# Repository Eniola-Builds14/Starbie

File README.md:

# Starbie
Starbie is a little robot pet with a star shaped PCB. It was designed using KICAD .I had alot of fun while building it and  I learned new things along the way. Starbie is a small project, but its my first step into PCB design.

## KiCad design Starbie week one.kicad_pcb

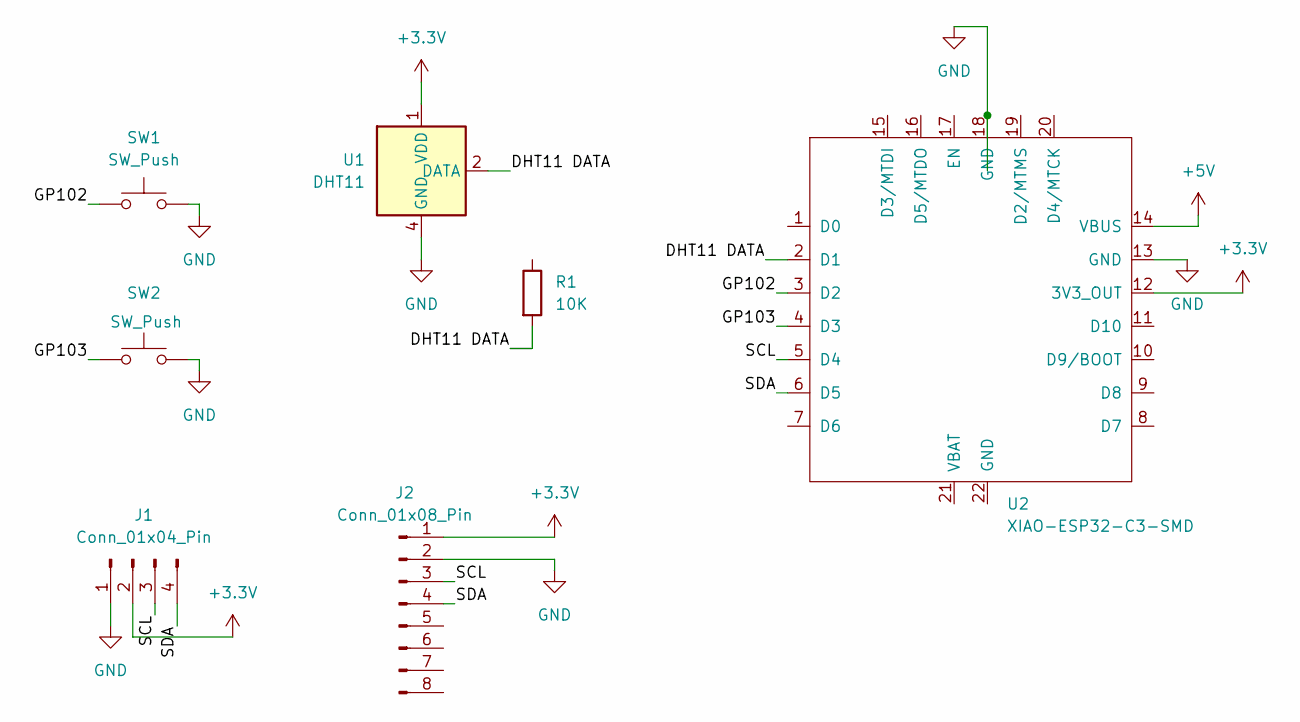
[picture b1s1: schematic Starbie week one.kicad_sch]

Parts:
J1: Conn_01x04_Pin; Display_128x64_096_I2C
J2: Conn_01x08_Pin; PinHeader_1x08_P2.54mm_Vertical
R1: 10K; R_Axial_DIN0204_L3.6mm_D1.6mm_P7.62mm_Horizontal
SW1, SW2: SW_Push; SW_Cherry_MX_1.00u_PCB
U1: DHT11; Aosong_DHT11_5.5x12.0_P2.54mm
U2: XIAO-ESP32-C3-SMD

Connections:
+3.3V: J1.2, J2.1, U1.1 (VDD), U2.12 (3V3_OUT)
+5V: U2.14 (VBUS)
/<NO NET>: SW2.1, U2.4 (D3)
/DHT11 DATA: R1.2, U1.2 (DATA), U2.2 (D1)
/GP102: SW1.1, U2.3 (D2)
/SCL: J1.3, J2.3, U2.5 (D4)
/SDA: J1.4, J2.4, U2.6 (D5)
GND: J1.1, J2.2, SW1.2, SW2.2, U1.4 (GND), U2.13 (GND), U2.18 (GND)

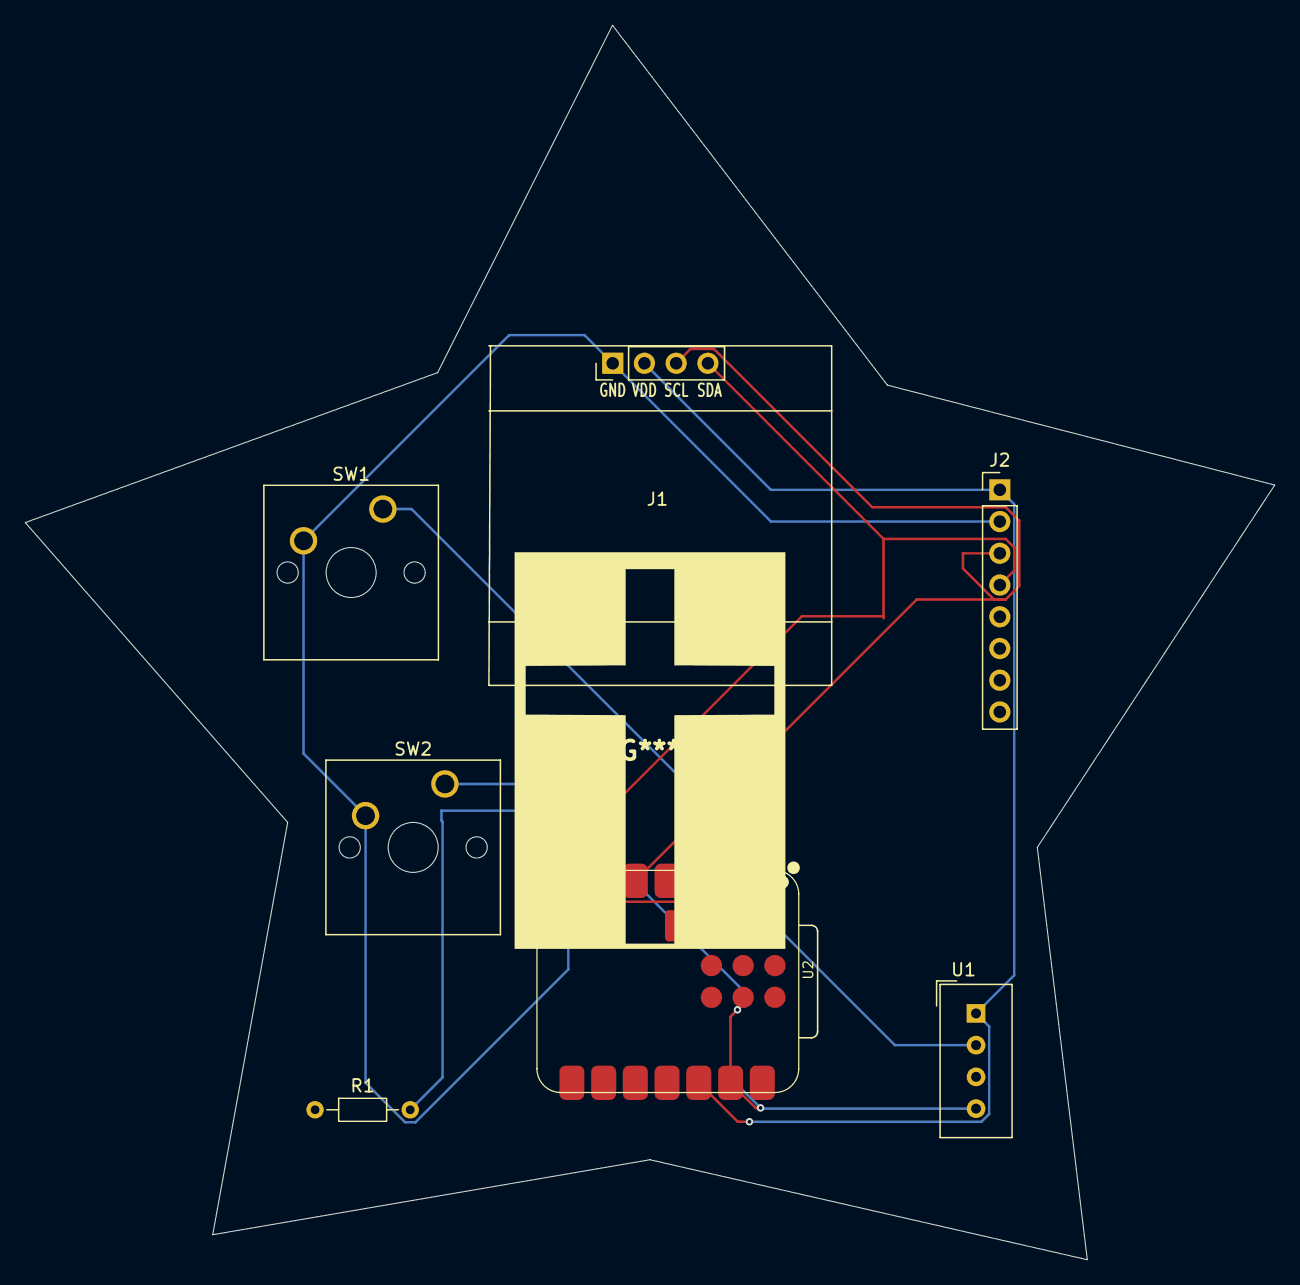
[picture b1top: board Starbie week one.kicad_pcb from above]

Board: 2 copper layers, 100.0 x 98.8 mm, 7 parts (0 on the bottom side), 7 nets.
